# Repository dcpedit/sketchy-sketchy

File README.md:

# Sketchy-Sketchy Keyboard

Below are some features of this keyboard:

* Fun case design based on the Etch-A-Sketch
* Layout focuses on only letters and numbers
* Use large ISO enter so that right hand can get the full set of home row keys (and it looks cool as well)
* 7u spacebar with no modifier keys to keep things clean and simple
* Dual rotary knobs (can be programmed to control horizontal and vertical mouse movements)
* Dual OLED screens, because why not

The OLED screens are not individually programmable. They’re tied to the same I2C outputs, so they just mirror each other.

## Supported layouts

[Keyboard Layout Editor](http://www.keyboard-layout-editor.com/#/gists/60673d2fd57cbc973ed444a9bf7b8208)

## Firmware ([Vial](https://get.vial.today))

The firmware source can be found in my fork of vial-qmk:

https://github.com/dcpedit/vial-qmk-dev/tree/vial/keyboards/dcpedit/sketchy

Pre-compiled binary (hex) can be found in the [`firmware`](https://github.com/dcpedit/sketchy-sketchy/tree/main/firmware) folder

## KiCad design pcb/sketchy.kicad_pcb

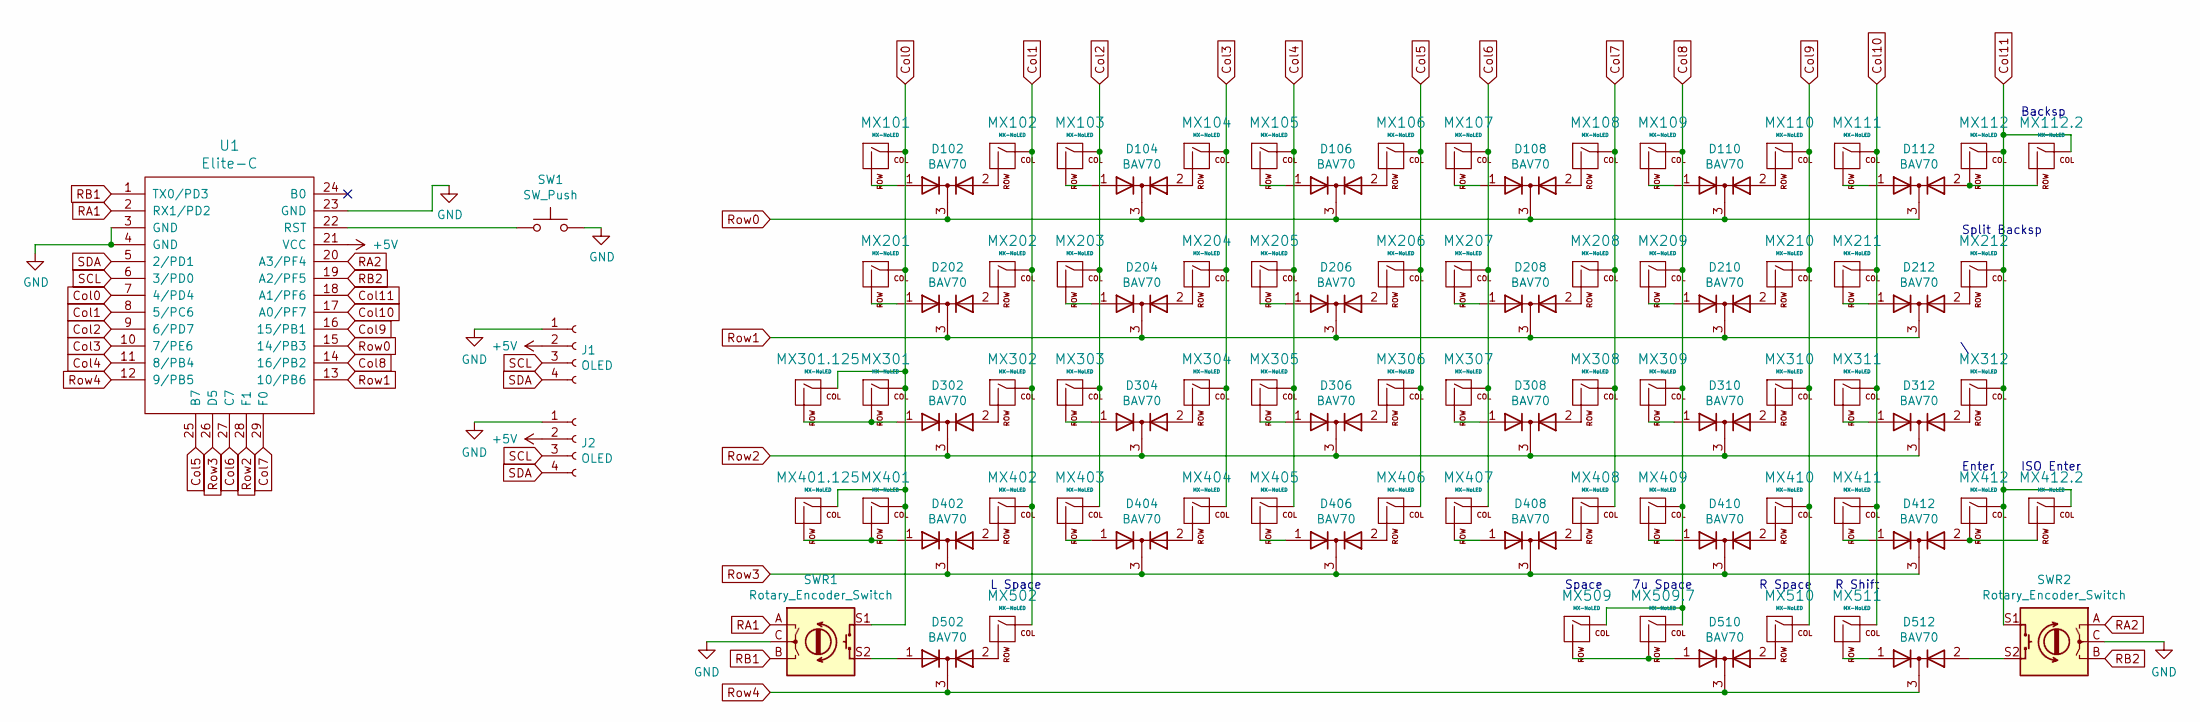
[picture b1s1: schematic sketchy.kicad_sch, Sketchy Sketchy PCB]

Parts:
D102, D104, D106, D108, D110, D112, D202, D204, D206, D208, D210, D212, D302, D304, D306, D308, D310, D312, D402, D404, D406, D408, D410, D412, D502, D510, D512: BAV70; SOT-23_Handsoldering
J1, J2: OLED; SSD1306_OLED
MX101, MX102, MX103, MX104, MX105, MX106, MX107, MX108, MX109, MX110, MX111, MX112, MX202, MX203, MX204, MX205, MX206, MX207, MX208, MX209, MX210, MX211, MX212, MX302, MX303, MX304, MX305, MX306, MX307, MX308, MX309, MX310, MX311, MX402, MX403, MX404, MX405, MX406, MX407, MX408, MX409, MX410, MX411: MX-NoLED; MXOnly-1U-Hotswap
MX112.2: MX-NoLED; MXOnly-2U-Hotswap
MX201, MX312: MX-NoLED; MXOnly-1.5U-Hotswap
MX301, MX511: MX-NoLED; MXOnly-1.75U-Hotswap
MX301.125, MX401.125, MX412: MX-NoLED; MXOnly-1.25U-Hotswap
MX401: MX-NoLED; MXOnly-2.25U-Hotswap
MX412.2: MX-NoLED; MXOnly-ISO-Hotswap
MX502: MX-NoLED; MXOnly-2U-Hotswap-ReversedStabilizers
MX509: MX-NoLED; MXOnly-2.25U-Hotswap-ReversedStabilizers
MX509.7: MX-NoLED; MXOnly-7U-Hotswap-ReversedStabilizers
MX510: MX-NoLED; MXOnly-2.75U-Hotswap-ReversedStabilizers
SW1: SW_Push; SW_Tactile_SPST_Angled_MJTP1117
SWR1, SWR2: Rotary_Encoder_Switch; RotaryEncoder_Alps_EC11E-Switch_Vertical_H20mm
U1: Elite-C

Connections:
+5V: J1.2, J2.2, U1.21 (VCC)
Col0: MX101.1 (COL), MX201.1 (COL), MX301.1 (COL), MX301.125.1 (COL), MX401.1 (COL), MX401.125.1 (COL), SWR1.S1, U1.7 (4/PD4)
Col1: MX102.1 (COL), MX202.1 (COL), MX302.1 (COL), MX402.1 (COL), MX502.1 (COL), U1.8 (5/PC6)
Col2: MX103.1 (COL), MX203.1 (COL), MX303.1 (COL), MX403.1 (COL), U1.9 (6/PD7)
Col3: MX104.1 (COL), MX204.1 (COL), MX304.1 (COL), MX404.1 (COL), U1.10 (7/PE6)
Col4: MX105.1 (COL), MX205.1 (COL), MX305.1 (COL), MX405.1 (COL), U1.11 (8/PB4)
Col5: MX106.1 (COL), MX206.1 (COL), MX306.1 (COL), MX406.1 (COL), U1.25 (B7)
Col6: MX107.1 (COL), MX207.1 (COL), MX307.1 (COL), MX407.1 (COL), U1.27 (C7)
Col7: MX108.1 (COL), MX208.1 (COL), MX308.1 (COL), MX408.1 (COL), U1.29 (F0)
Col8: MX109.1 (COL), MX209.1 (COL), MX309.1 (COL), MX409.1 (COL), MX509.1 (COL), MX509.7.1 (COL), U1.14 (16/PB2)
Col9: MX110.1 (COL), MX210.1 (COL), MX310.1 (COL), MX410.1 (COL), MX510.1 (COL), U1.16 (15/PB1)
Col10: MX111.1 (COL), MX211.1 (COL), MX311.1 (COL), MX411.1 (COL), MX511.1 (COL), U1.17 (A0/PF7)
Col11: MX112.1 (COL), MX112.2.1 (COL), MX212.1 (COL), MX312.1 (COL), MX412.1 (COL), MX412.2.1 (COL), SWR2.S1, U1.18 (A1/PF6)
GND: J1.1, J2.1, SW1.2, SWR1.C, SWR2.C, U1.3 (GND), U1.4 (GND), U1.23 (GND)
unnamed: D102.1 (A), MX101.2 (ROW)
unnamed: D102.2 (A), MX102.2 (ROW)
unnamed: D104.1 (A), MX103.2 (ROW)
unnamed: D104.2 (A), MX104.2 (ROW)
unnamed: D106.1 (A), MX105.2 (ROW)
unnamed: D106.2 (A), MX106.2 (ROW)
unnamed: D108.1 (A), MX107.2 (ROW)
unnamed: D108.2 (A), MX108.2 (ROW)
unnamed: D110.1 (A), MX109.2 (ROW)
unnamed: D110.2 (A), MX110.2 (ROW)
unnamed: D112.1 (A), MX111.2 (ROW)
unnamed: D112.2 (A), MX112.2 (ROW), MX112.2.2 (ROW)
unnamed: D202.1 (A), MX201.2 (ROW)
unnamed: D202.2 (A), MX202.2 (ROW)
unnamed: D204.1 (A), MX203.2 (ROW)
unnamed: D204.2 (A), MX204.2 (ROW)
unnamed: D206.1 (A), MX205.2 (ROW)
unnamed: D206.2 (A), MX206.2 (ROW)
unnamed: D208.1 (A), MX207.2 (ROW)
unnamed: D208.2 (A), MX208.2 (ROW)
unnamed: D210.1 (A), MX209.2 (ROW)
unnamed: D210.2 (A), MX210.2 (ROW)
unnamed: D212.1 (A), MX211.2 (ROW)
unnamed: D212.2 (A), MX212.2 (ROW)
unnamed: D302.1 (A), MX301.2 (ROW), MX301.125.2 (ROW)
unnamed: D302.2 (A), MX302.2 (ROW)
unnamed: D304.1 (A), MX303.2 (ROW)
unnamed: D304.2 (A), MX304.2 (ROW)
unnamed: D306.1 (A), MX305.2 (ROW)
unnamed: D306.2 (A), MX306.2 (ROW)
unnamed: D308.1 (A), MX307.2 (ROW)
unnamed: D308.2 (A), MX308.2 (ROW)
unnamed: D310.1 (A), MX309.2 (ROW)
unnamed: D310.2 (A), MX310.2 (ROW)
unnamed: D312.1 (A), MX311.2 (ROW)
unnamed: D312.2 (A), MX312.2 (ROW)
unnamed: D402.1 (A), MX401.2 (ROW), MX401.125.2 (ROW)
unnamed: D402.2 (A), MX402.2 (ROW)
unnamed: D404.1 (A), MX403.2 (ROW)
unnamed: D404.2 (A), MX404.2 (ROW)
unnamed: D406.1 (A), MX405.2 (ROW)
unnamed: D406.2 (A), MX406.2 (ROW)
unnamed: D408.1 (A), MX407.2 (ROW)
unnamed: D408.2 (A), MX408.2 (ROW)
unnamed: D410.1 (A), MX409.2 (ROW)
unnamed: D410.2 (A), MX410.2 (ROW)
unnamed: D412.1 (A), MX411.2 (ROW)
unnamed: D412.2 (A), MX412.2 (ROW), MX412.2.2 (ROW)
unnamed: D502.1 (A), SWR1.S2
unnamed: D502.2 (A), MX502.2 (ROW)
unnamed: D510.1 (A), MX509.2 (ROW), MX509.7.2 (ROW)
unnamed: D510.2 (A), MX510.2 (ROW)
unnamed: D512.1 (A), MX511.2 (ROW)
unnamed: D512.2 (A), SWR2.S2
unnamed: SW1.1, U1.22 (RST)
RA1: SWR1.A, U1.2 (RX1/PD2)
RA2: SWR2.A, U1.20 (A3/PF4)
RB1: SWR1.B, U1.1 (TX0/PD3)
RB2: SWR2.B, U1.19 (A2/PF5)
Row0: D102.3 (K), D104.3 (K), D106.3 (K), D108.3 (K), D110.3 (K), D112.3 (K), U1.15 (14/PB3)
Row1: D202.3 (K), D204.3 (K), D206.3 (K), D208.3 (K), D210.3 (K), D212.3 (K), U1.13 (10/PB6)
Row2: D302.3 (K), D304.3 (K), D306.3 (K), D308.3 (K), D310.3 (K), D312.3 (K), U1.28 (F1)
Row3: D402.3 (K), D404.3 (K), D406.3 (K), D408.3 (K), D410.3 (K), D412.3 (K), U1.26 (D5)
Row4: D502.3 (K), D510.3 (K), D512.3 (K), U1.12 (9/PB5)
SCL: J1.3, J2.3, U1.6 (3/PD0)
SDA: J1.4, J2.4, U1.5 (2/PD1)

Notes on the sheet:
Space
L Space
7u Space
Enter
ISO Enter
Split Backsp
Backsp
R Space
R Shift

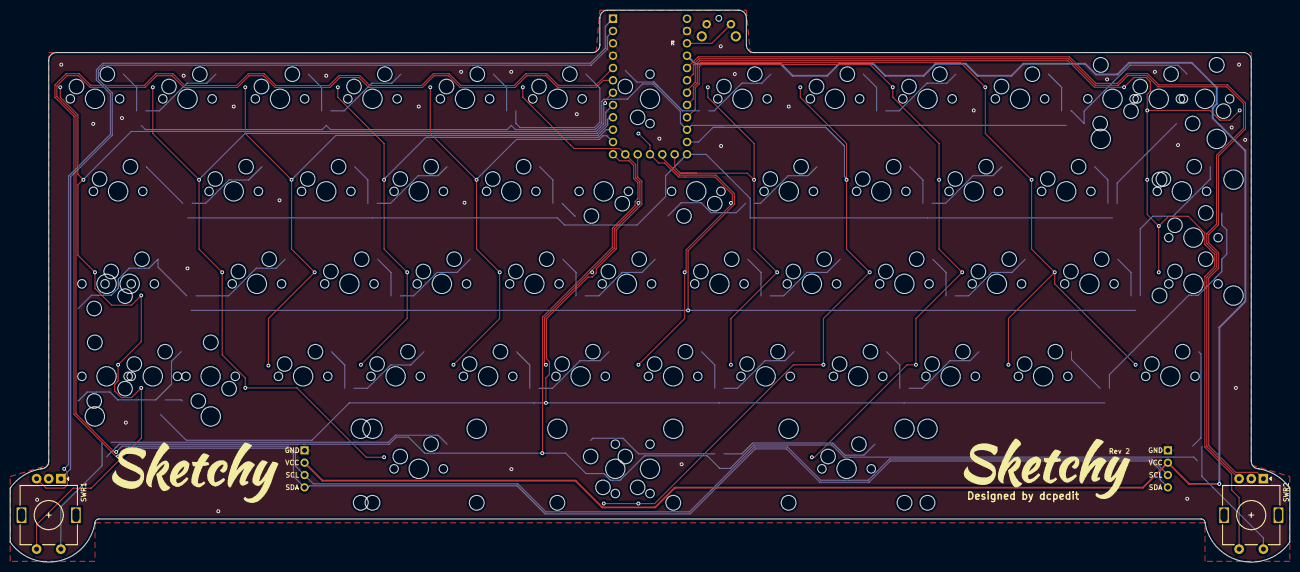
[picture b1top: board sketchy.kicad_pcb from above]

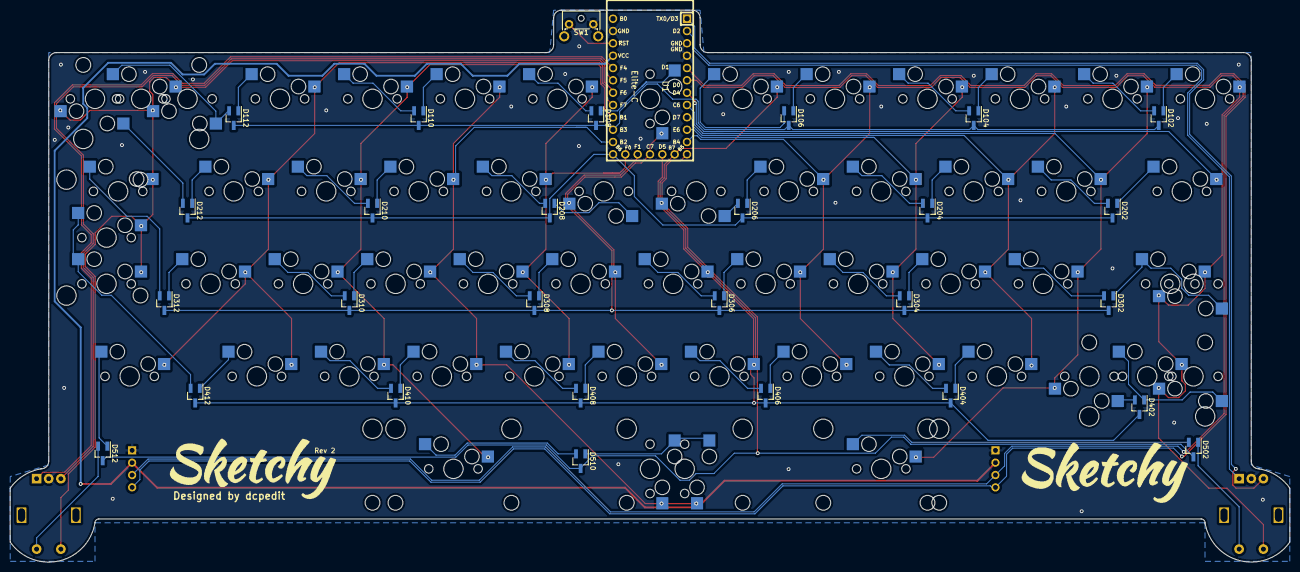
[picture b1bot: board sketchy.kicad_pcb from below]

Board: 2 copper layers, 263.5 x 113.7 mm, 90 parts (28 on the bottom side), 80 nets.

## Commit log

2022-11-22 Case files updated
2022-12-15 Update build guide
2022-12-16 Update readmes
2023-01-17 DXF version of case file
2023-02-01 Add Vial binary
2023-11-03 Update README.md source link
